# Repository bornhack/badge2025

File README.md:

# BornHack 2025 Circle Badge with LoRa

")

This badge focuses on LoRa and wireless communication in general, as there are also WiFi and Bluetooth Low Energy included in the ESP32-C3 module.

It's a relatively bare bone design, with pretty much just the minimum elements to run a Meshtastic node or similar device.

Even though there is an antenna on the PCB for LoRa (868MHz) it's unfortunately not connected as the [LoRa module](https://www.seeedstudio.com/Wio-SX1262-Wireless-Module-p-5981.html) is the variant that has a connector (uf.L/IPEX), so an [external antenna](https://www.molex.com/en-us/products/part-detail/2111400100) is provided in the kit, that is designed to match with the connector on the module. The external antenna has selfadhesive backing, but don't mount it to the PCB, as most of the PCB is covered with copper, which will heavily decrese the performance, so if you want to stick it to something, better use a plastic case or similar.

The badge comes preinstalled with [Meshtastic](https://meshtastic.org/) firmware, that you can hook up to and configure using the Mestastic app on your phone (Android or iOS). The two apps are slightly different, but does have more or less the same overall features.

If you want to use Meshtastic for a longer period, it's recommended to power the badge via USB-C (simple  5V, eg. power bank or power adapter).

In addition to the LoRa module, there are 5 RGB LEDs on the side, a qwiic/StemmaQT connector and a footprint for a SAO v1.69bis connector for expansions, mostly for alternative firmwares.

## 3D Printable case

In the ```case``` folder is a desing, done in OpenSCAD, for a half or back case, that snaps on to the PCB and covers the back part with the battery holders, antenna and LEDs.

There are two versions, one fully closed, and one with a cutout for mounting it on a wall using a screw.

Both should print on most FDM printers without the need for support, with the back side facing down on the build plate.

## Projects running on the badge

Feel free to submit a PR adding on to this list with your project that runs on the badge.

- [Initial Meshtastic firmware](https://github.com/badgeteam/bornhack2025-meshtastic) ([Flasher tool](https://github.com/badgeteam/bornhack2025-flasher))
- [Zephyr device tree](https://cyberchaos.dev/kloenk/bornhack-2025-badge) (no actually firmware, just support files)
- _project name and link to more info_

## Designed in KiCad v9

To open the project, you will need to install a recent release version or one of the nightly builds, KiCad v8 or earlier won't open this design. The [schematic as a PDF](https://github.com/bornhack/badge2025/raw/main/schematics.pdf) is included for reference.

## License

The hardware design of the `main` branch of this repository is released under the following license:

* the "Creative Commons Attribution-ShareAlike 4.0 International License"
  (CC BY-SA 4.0) full text of this license is included in the LICENSE file
  and a copy can also be found at
  [http://creativecommons.org/licenses/by-sa/4.0/](http://creativecommons.org/licenses/by-sa/4.0/)

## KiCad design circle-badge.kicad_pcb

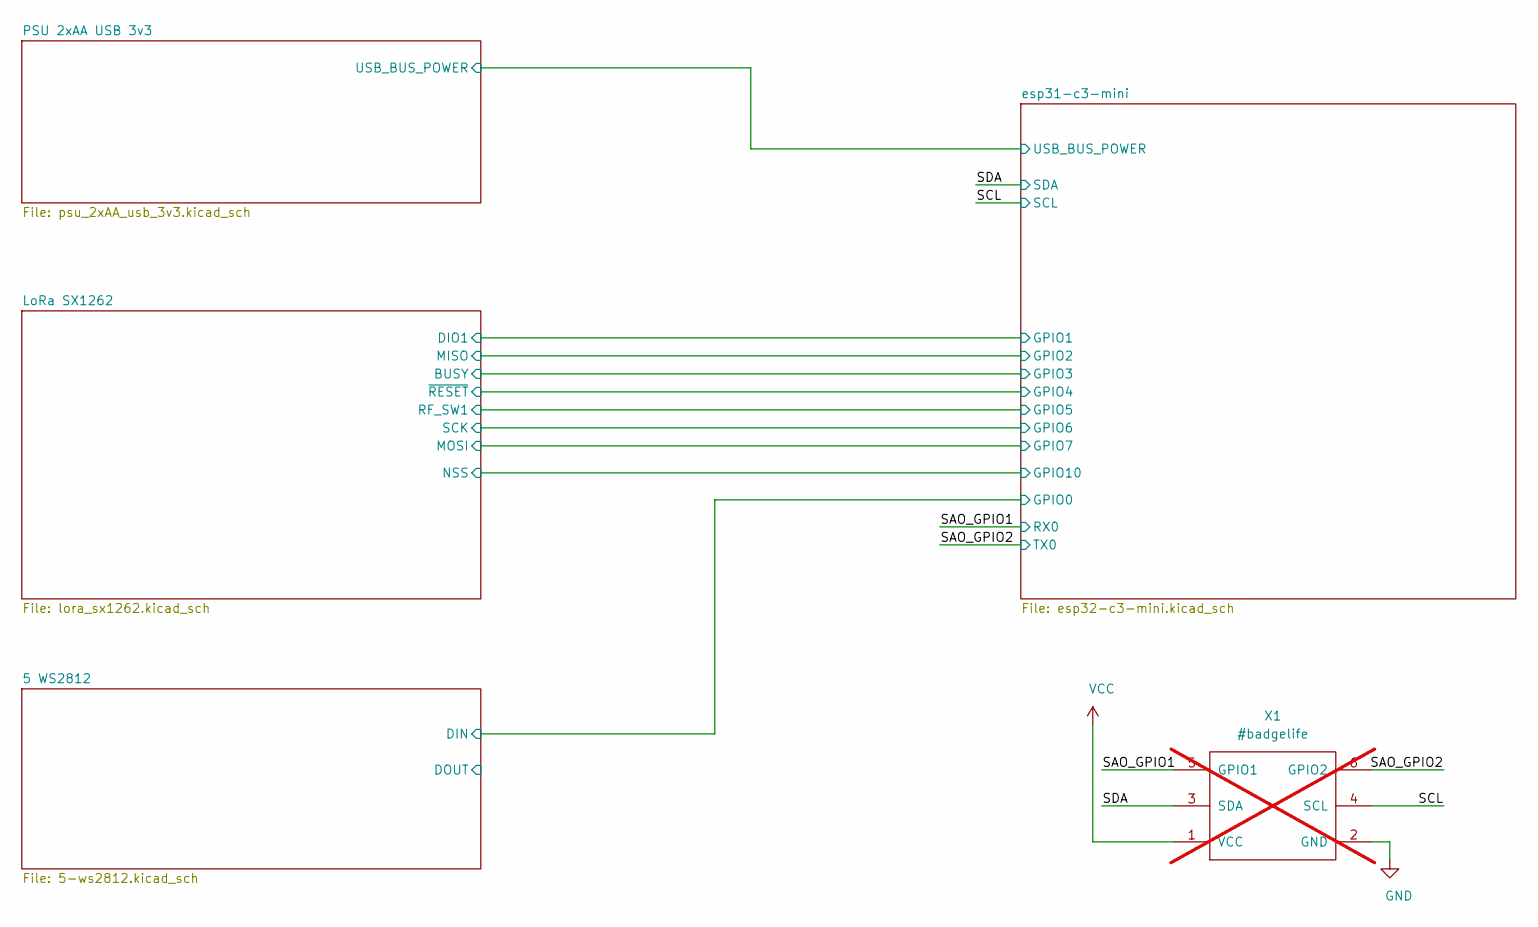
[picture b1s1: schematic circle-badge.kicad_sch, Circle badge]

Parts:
X1: #badgelife; Badgelife-SAOv169-BADGE-2x3; not fitted

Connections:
/SAO_GPIO1: X1.5 (GPIO1); also elsewhere on the board
/SAO_GPIO2: X1.6 (GPIO2); also elsewhere on the board
/SCL: X1.4 (SCL); also elsewhere on the board
/SDA: X1.3 (SDA); also elsewhere on the board
GND: X1.2 (GND); also elsewhere on the board
VCC: X1.1 (VCC); also elsewhere on the board

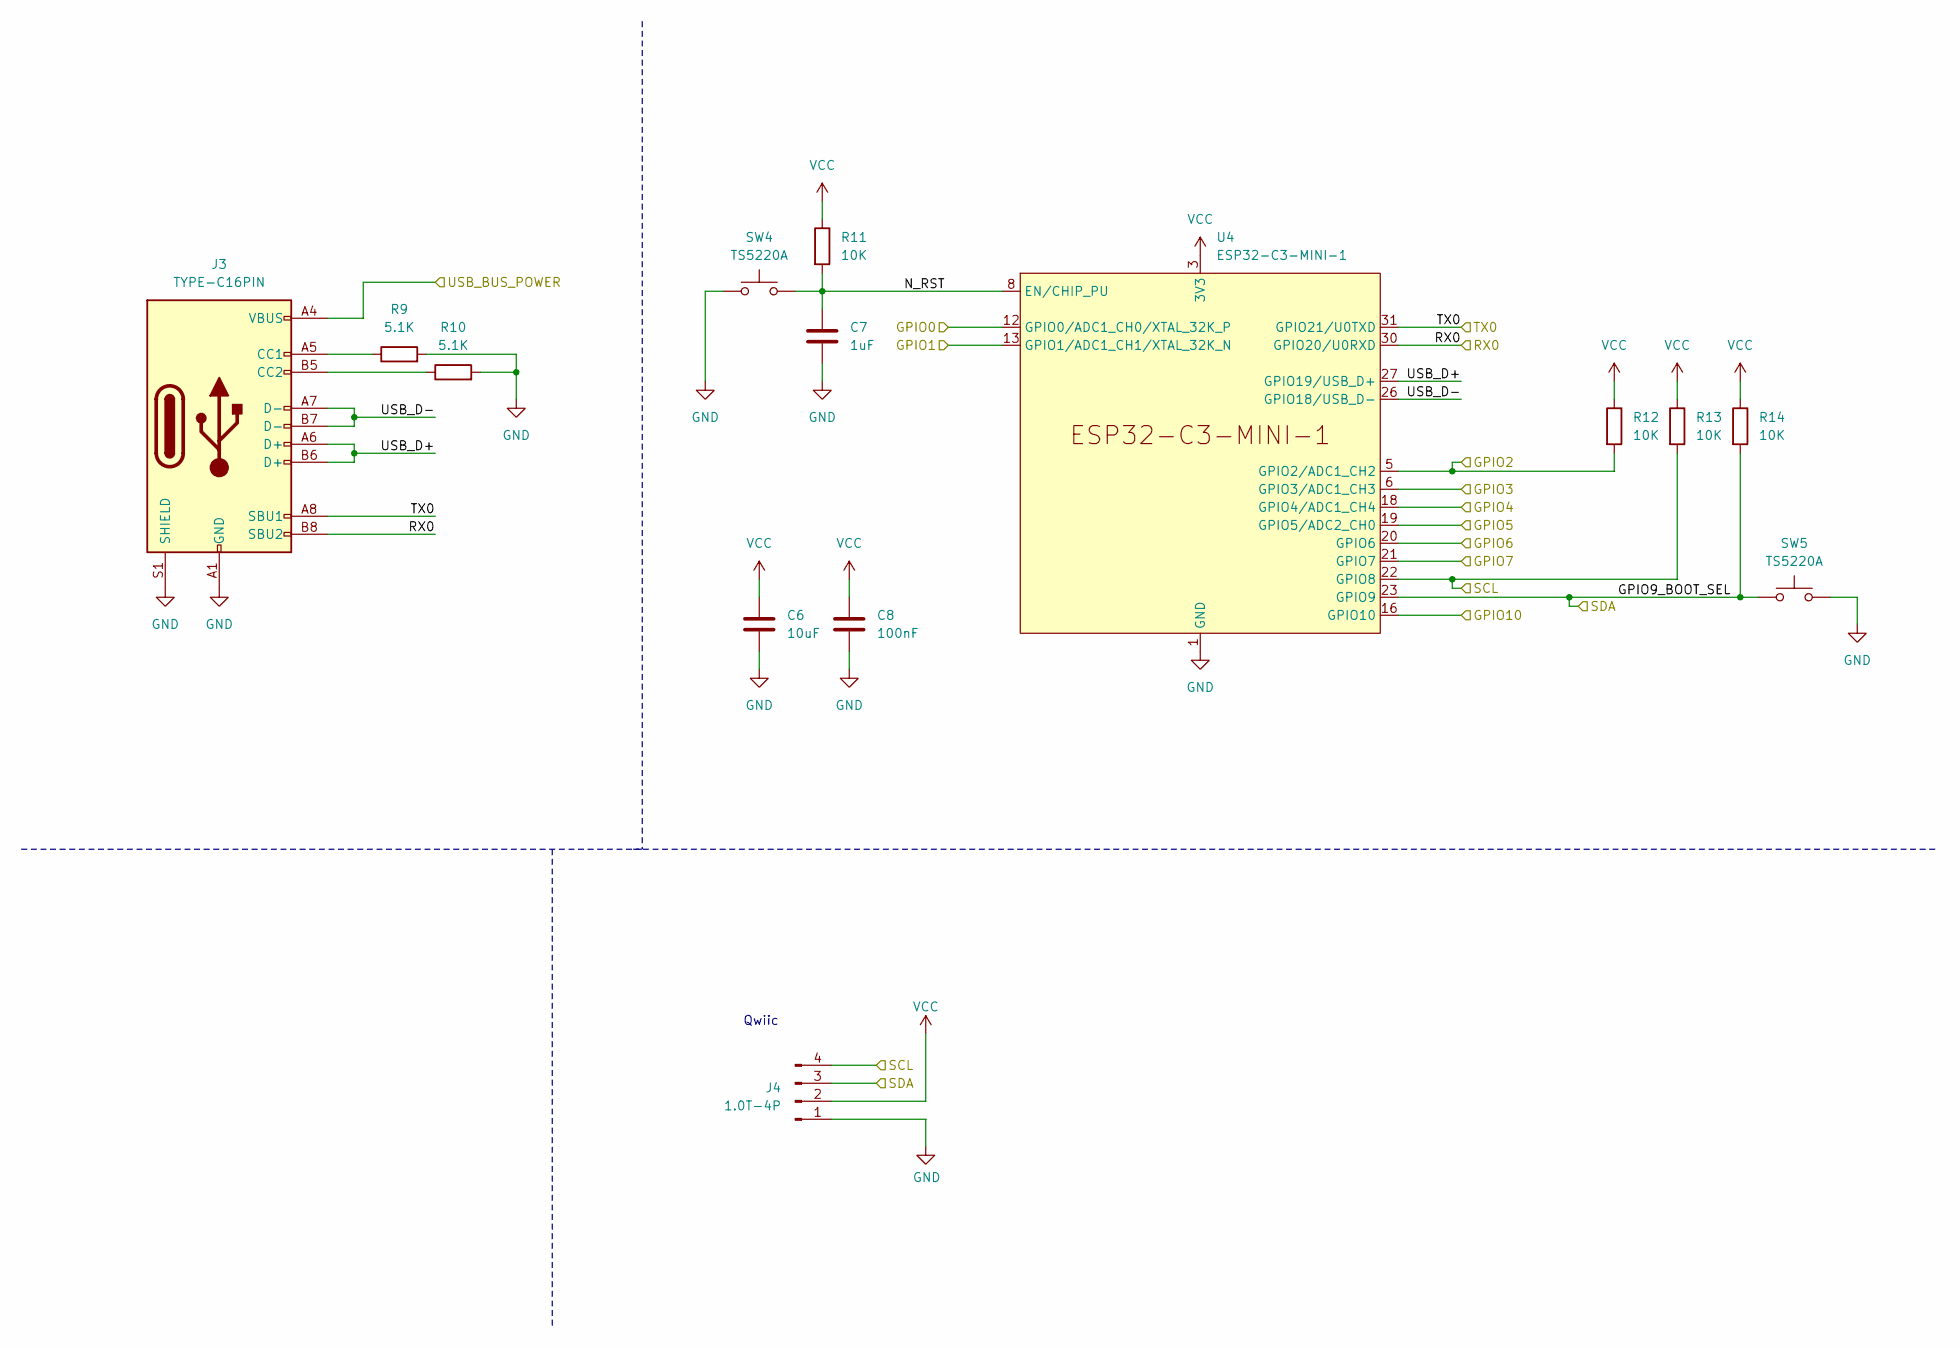
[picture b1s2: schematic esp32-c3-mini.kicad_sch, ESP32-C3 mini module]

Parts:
C6: 10uF; C_0603_1608Metric
C7: 1uF; C_0603_1608Metric
C8: 100nF; C_0603_1608Metric
J3: TYPE-C16PIN; USB_C_Receptacle_XKB_U262-16XN-4BVC11; LCSC C393939
J4: 1.0T-4P; JST_SH_SM04B-SRSS-TB_1x04-1MP_P1.00mm_Horizontal; LCSC C145956
R9, R10: 5.1K; R_0603_1608Metric
R11, R12, R13, R14: 10K; R_0603_1608Metric
SW4, SW5: TS5220A; SW_SPST_TL3342; LCSC C412370
U4: ESP32-C3-MINI-1

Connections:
/5 WS2812/DIN: U4.12 (GPIO0/ADC1_CH0/XTAL_32K_P); also elsewhere on the board
/LoRa SX1262/BUSY: U4.6 (GPIO3/ADC1_CH3); also elsewhere on the board
/LoRa SX1262/DIO1: U4.13 (GPIO1/ADC1_CH1/XTAL_32K_N); also elsewhere on the board
/LoRa SX1262/MISO: R12.2, U4.5 (GPIO2/ADC1_CH2); also elsewhere on the board
/LoRa SX1262/MOSI: U4.21 (GPIO7); also elsewhere on the board
/LoRa SX1262/NSS: U4.16 (GPIO10); also elsewhere on the board
/LoRa SX1262/RF_SW1: U4.19 (GPIO5/ADC2_CH0); also elsewhere on the board
/LoRa SX1262/SCK: U4.20 (GPIO6); also elsewhere on the board
/LoRa SX1262/~RESET: U4.18 (GPIO4/ADC1_CH4); also elsewhere on the board
/PSU 2xAA USB 3v3/USB_BUS_POWER: J3.A4 (VBUS), J3.A9 (VBUS), J3.B4 (VBUS), J3.B9 (VBUS); also elsewhere on the board
/SAO_GPIO1: J3.B8 (SBU2), U4.30 (GPIO20/U0RXD); also elsewhere on the board
/SAO_GPIO2: J3.A8 (SBU1), U4.31 (GPIO21/U0TXD); also elsewhere on the board
/SCL: J4.4, R13.2, U4.22 (GPIO8); also elsewhere on the board
/SDA: J4.3, R14.2, SW5.1, U4.23 (GPIO9); also elsewhere on the board
/esp31-c3-mini/N_RST: C7.1, R11.2, SW4.2, U4.8 (EN/CHIP_PU)
/esp31-c3-mini/USB_D+: J3.A6 (D+), J3.B6 (D+), U4.27 (GPIO19/USB_D+)
/esp31-c3-mini/USB_D-: J3.A7 (D-), J3.B7 (D-), U4.26 (GPIO18/USB_D-)
GND: C6.2, C7.2, C8.2, J3.A1 (GND), J3.A12 (GND), J3.B1 (GND), J3.B12 (GND), J3.S1 (SHIELD), J4.1, R9.2, R10.2, SW4.1, SW5.2, U4.1 (GND), U4.2 (GND), U4.11 (GND), U4.14 (GND), U4.36 (GND), U4.37 (GND), U4.38 (GND), U4.39 (GND), U4.40 (GND), U4.41 (GND), U4.42 (GND), U4.43 (GND), U4.44 (GND), U4.45 (GND), U4.46 (GND), U4.47 (GND), U4.48 (GND), U4.49 (GND), U4.50 (GND), U4.51 (GND), U4.52 (GND), U4.53 (GND); also elsewhere on the board
unnamed: J3.A5 (CC1), R9.1
unnamed: J3.B5 (CC2), R10.1
VCC: C6.1, C8.1, J4.2, R11.1, R12.1, R13.1, R14.1, U4.3 (3V3); also elsewhere on the board

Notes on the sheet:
Qwiic

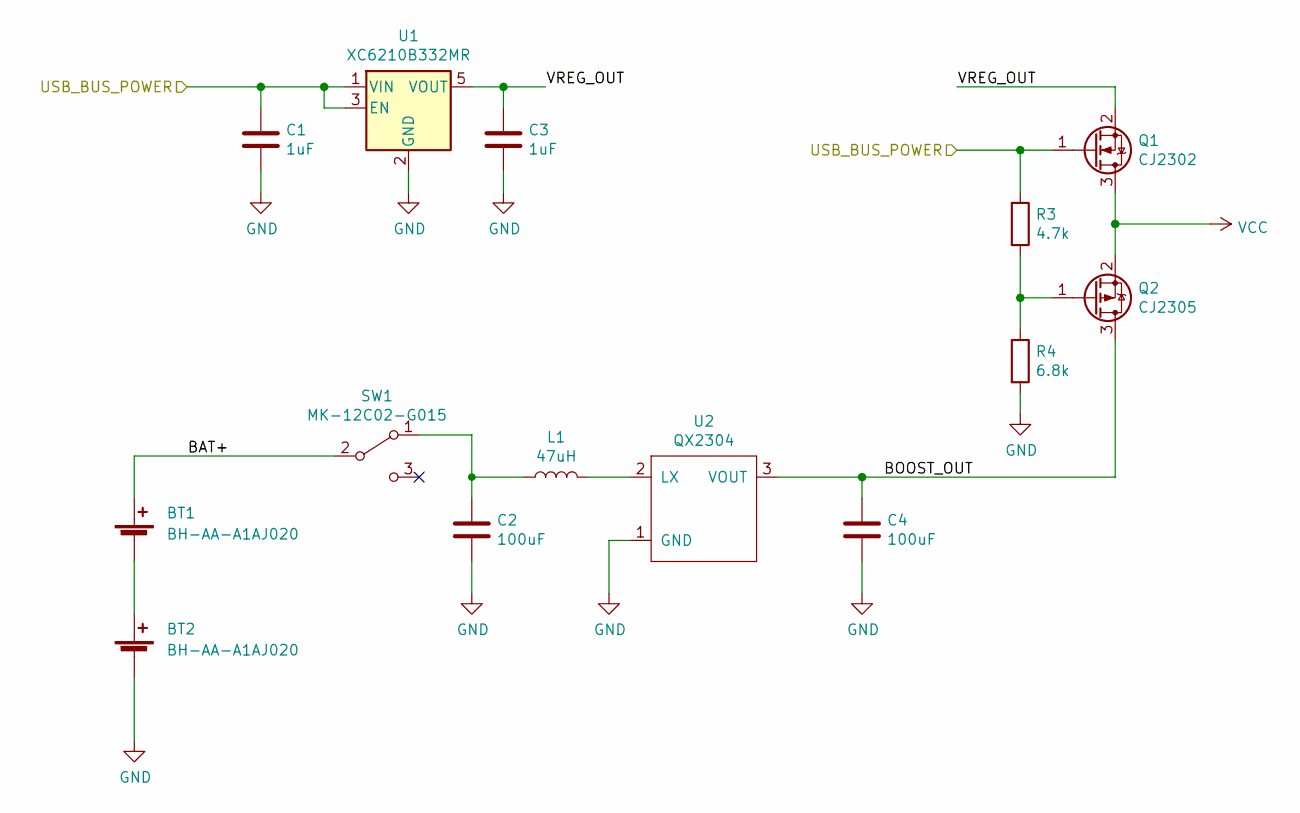
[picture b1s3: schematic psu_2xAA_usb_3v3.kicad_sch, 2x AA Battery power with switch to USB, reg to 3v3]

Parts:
BT1, BT2: BH-AA-A1AJ020; Single_AA; LCSC C5290181
C1, C3: 1uF; C_0603_1608Metric
C2, C4: 100uF; C_1206_3216Metric
L1: 47uH; L_1210_3225Metric
Q1: CJ2302; SOT-23; LCSC C8548
Q2: CJ2305; SOT-23; LCSC C8549
R3: 4.7k; R_0603_1608Metric
R4: 6.8k; R_0603_1608Metric
SW1: MK-12C02-G015; SW_SPDT_PCM12; LCSC C2911519
U1: XC6210B332MR; SOT-23-5; LCSC C3021084
U2: QX2304; SOT-23; LCSC C219038

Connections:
/PSU 2xAA USB 3v3/BAT+: BT1.1 (+), SW1.2 (B)
/PSU 2xAA USB 3v3/BOOST_OUT: C4.1, Q2.3 (D), U2.3 (VOUT)
/PSU 2xAA USB 3v3/USB_BUS_POWER: C1.1, Q1.1 (G), R3.1, U1.1 (VIN), U1.3 (EN); also elsewhere on the board
/PSU 2xAA USB 3v3/VREG_OUT: C3.1, Q1.2 (S), U1.5 (VOUT)
GND: BT2.2 (-), C1.2, C2.2, C3.2, C4.2, R4.2, U1.2 (GND), U2.1 (GND); also elsewhere on the board
unnamed: BT1.2 (-), BT2.1 (+)
unnamed: Q2.1 (G), R3.2, R4.1
unnamed: C2.1, L1.1, SW1.1 (A)
unnamed: L1.2, U2.2 (LX)
VCC: Q1.3 (D), Q2.2 (S); also elsewhere on the board

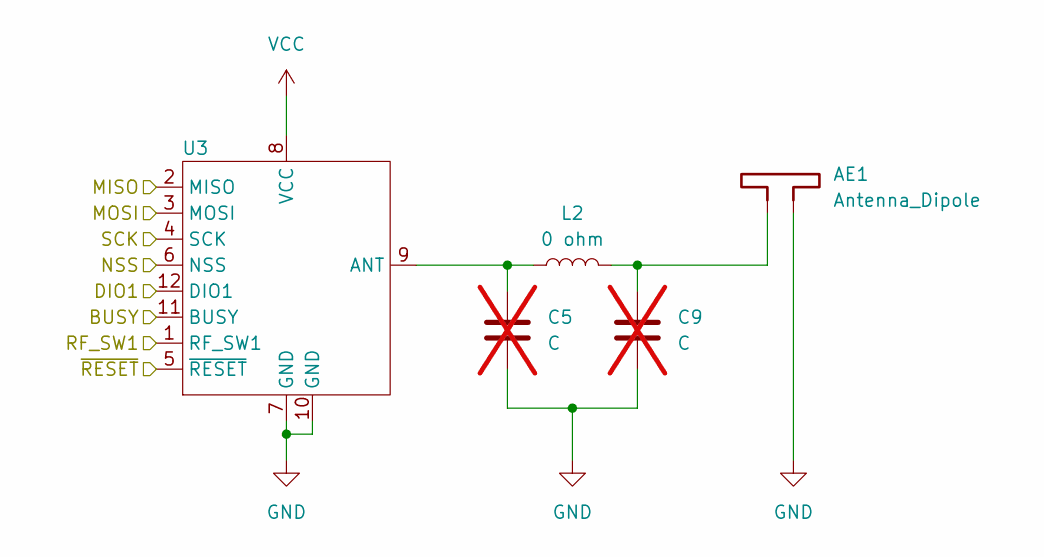
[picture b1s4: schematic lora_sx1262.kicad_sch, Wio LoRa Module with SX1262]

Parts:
AE1: Antenna_Dipole; 868 Inverted F Antenna
C5, C9: C; C_0603_1608Metric; not fitted
L2: 0 ohm; L_0603_1608Metric
U3: Wio-SX1262 / 113991436; MODULE12P-1.27-11X11.6MM

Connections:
/LoRa SX1262/BUSY: U3.11 (BUSY); also elsewhere on the board
/LoRa SX1262/DIO1: U3.12 (DIO1); also elsewhere on the board
/LoRa SX1262/MISO: U3.2 (MISO); also elsewhere on the board
/LoRa SX1262/MOSI: U3.3 (MOSI); also elsewhere on the board
/LoRa SX1262/NSS: U3.6 (NSS); also elsewhere on the board
/LoRa SX1262/RF_SW1: U3.1 (RF_SW1); also elsewhere on the board
/LoRa SX1262/SCK: U3.4 (SCK); also elsewhere on the board
/LoRa SX1262/~RESET: U3.5 (~RESET); also elsewhere on the board
GND: AE1.2, C5.2, C9.2, U3.7 (GND), U3.10 (GND); also elsewhere on the board
unnamed: AE1.1, C9.1, L2.2
unnamed: C5.1, L2.1, U3.9 (ANT)
VCC: U3.8 (VCC); also elsewhere on the board

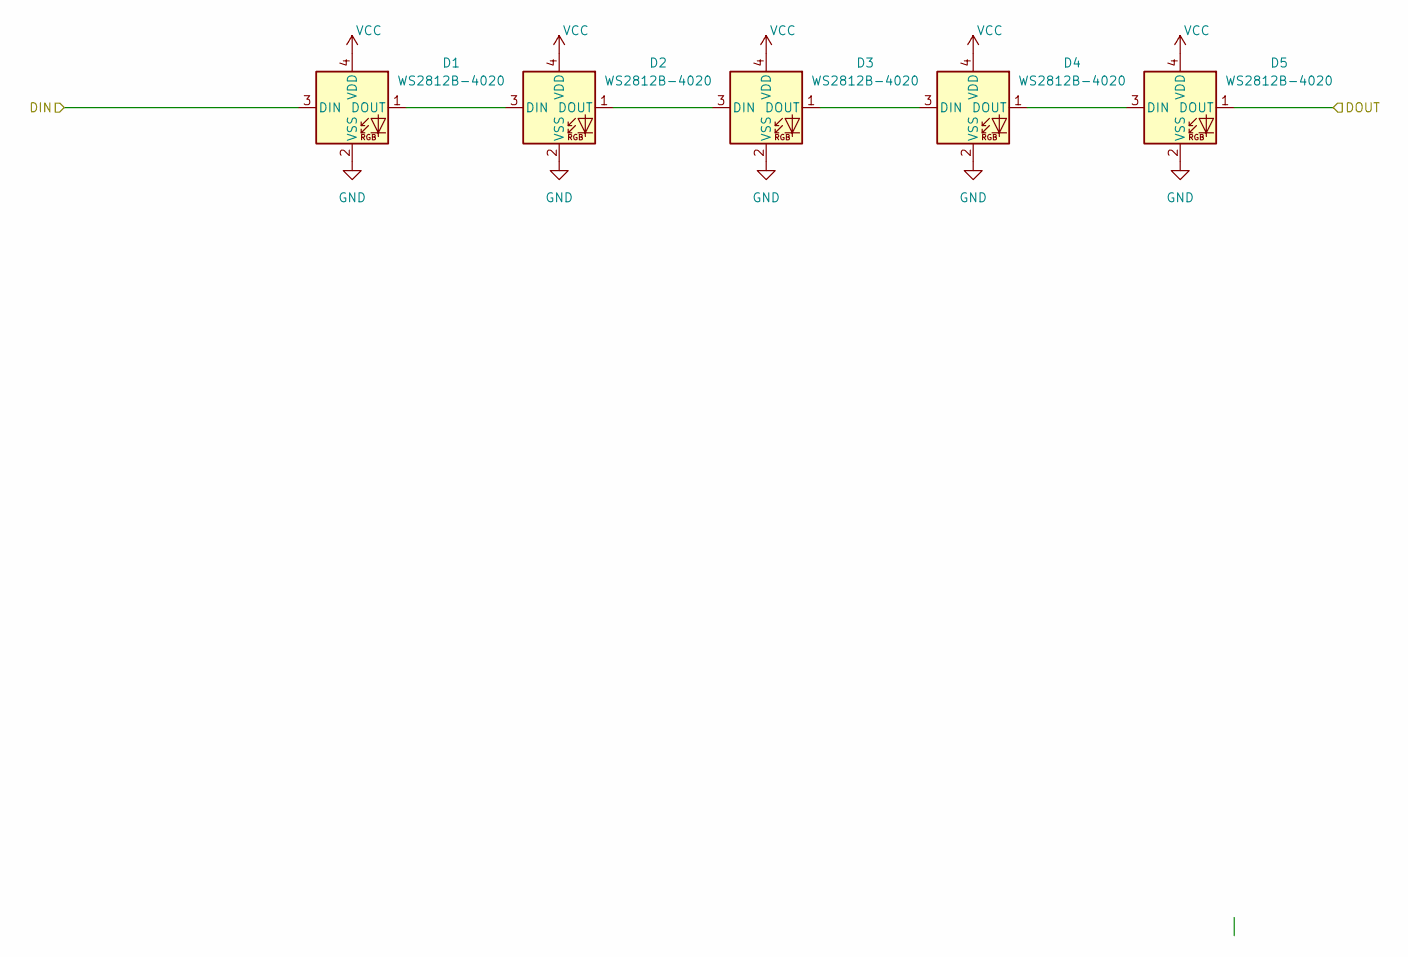
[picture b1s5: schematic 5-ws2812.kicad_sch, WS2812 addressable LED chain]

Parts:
D1, D2, D3, D4, D5: WS2812B-4020; LCSC C965557

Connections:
/5 WS2812/DIN: D1.3 (DIN); also elsewhere on the board
/5 WS2812/DOUT: D5.1 (DOUT)
GND: D1.2 (VSS), D2.2 (VSS), D3.2 (VSS), D4.2 (VSS), D5.2 (VSS); also elsewhere on the board
unnamed: D1.1 (DOUT), D2.3 (DIN)
unnamed: D2.1 (DOUT), D3.3 (DIN)
unnamed: D3.1 (DOUT), D4.3 (DIN)
unnamed: D4.1 (DOUT), D5.3 (DIN)
VCC: D1.4 (VDD), D2.4 (VDD), D3.4 (VDD), D4.4 (VDD), D5.4 (VDD); also elsewhere on the board

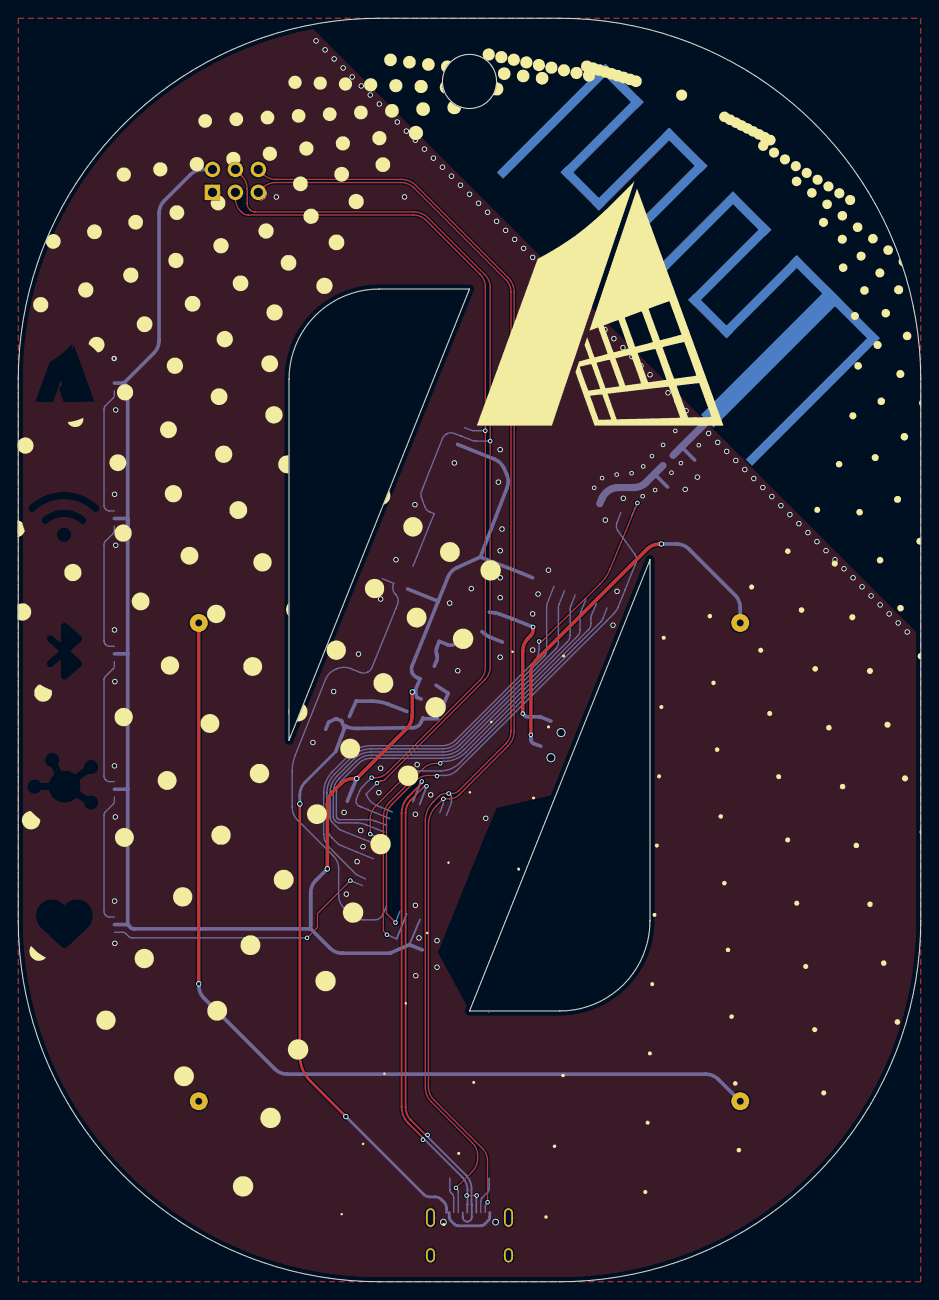
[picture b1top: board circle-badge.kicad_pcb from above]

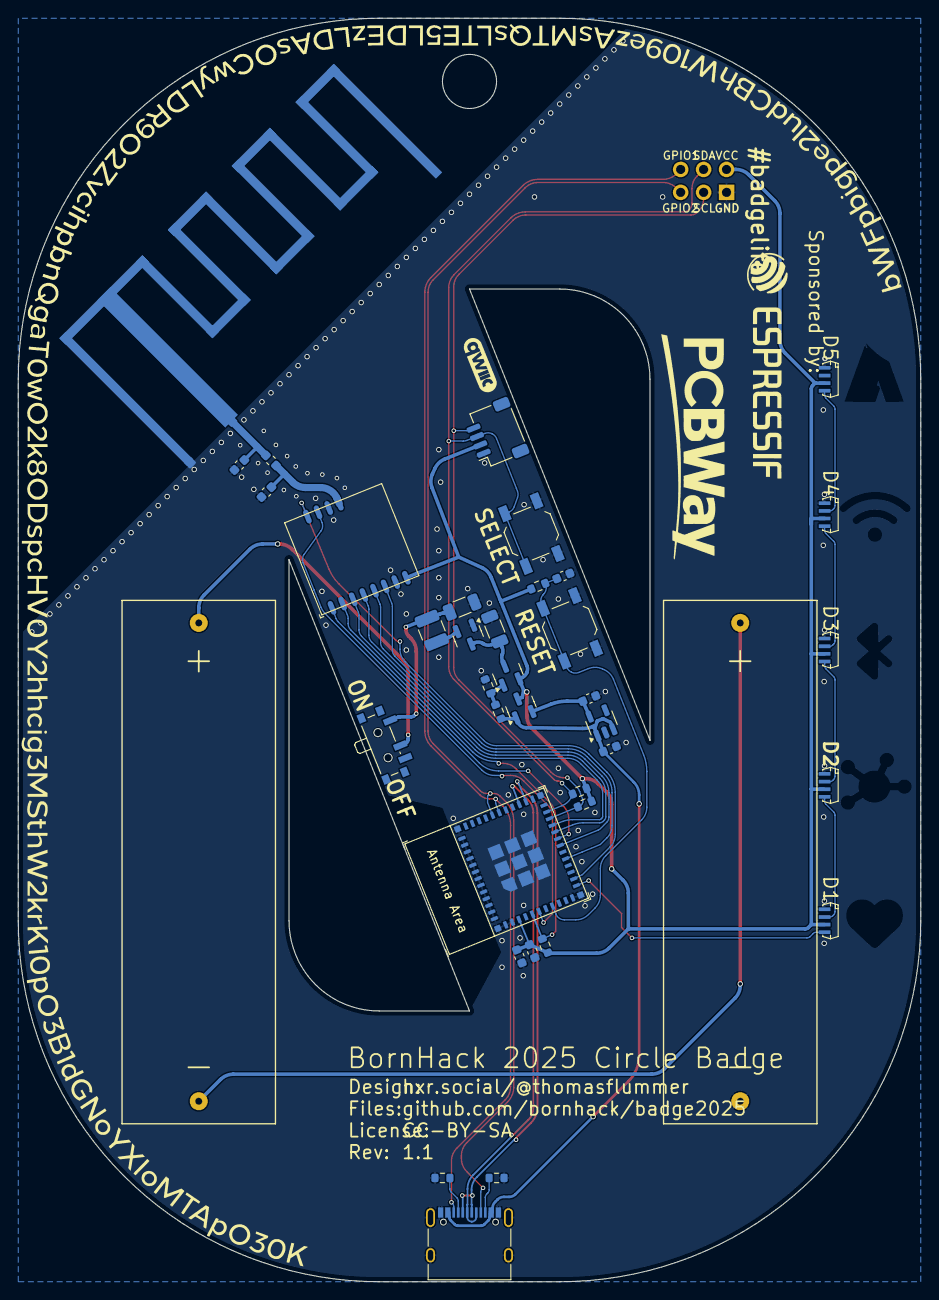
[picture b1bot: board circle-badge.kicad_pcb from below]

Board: 2 copper layers, 100.0 x 140.0 mm, 39 parts (38 on the bottom side), 34 nets.

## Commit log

2025-04-28 Initial version
2025-06-08 Added front artwork and token on the back
    Also:
    - Tweaked the trace to the antenna to hopefully better match 50ohm impedance
    - Tweaked all traces to use fillet on all corners
    - Added/fixed parts information
2025-06-09 Changed mask layer for USB-C connector
    Made sure mask bridges are 0.22mm wide
2025-07-21 Added readme and documentation
2025-08-08 add link to zephyr device tree
    Add a link to zephyr device trees that can be used to write firmware with zephyr[0] on the badge
    [0]: https://zephyrproject.org/
2025-08-08 Added case design
2025-08-16 Added MeshCore
